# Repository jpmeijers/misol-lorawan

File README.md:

# LoRa Weather Station

__THIS IS STILL A WORK IN PROGRESS__

This repo contains a design for a replacement PCB for a MISOL weather station. The replacement PCB fits in the same space and enclosure as the original transmitter board. It sends the sensor data via a LoRa radio. The new PCB supports LoRaWAN and can send the data to a network like The Things Network.

The PCB design is done using KiCad.

# References

http://www.misolie.net/weather-station-c-43.html

https://www.robotics.org.za/WH-SP-WS02

https://www.sparkfun.com/products/8942

https://cdn.sparkfun.com/assets/8/4/c/d/6/Weather_Sensor_Assembly_Updated.pdf

# Original PCB

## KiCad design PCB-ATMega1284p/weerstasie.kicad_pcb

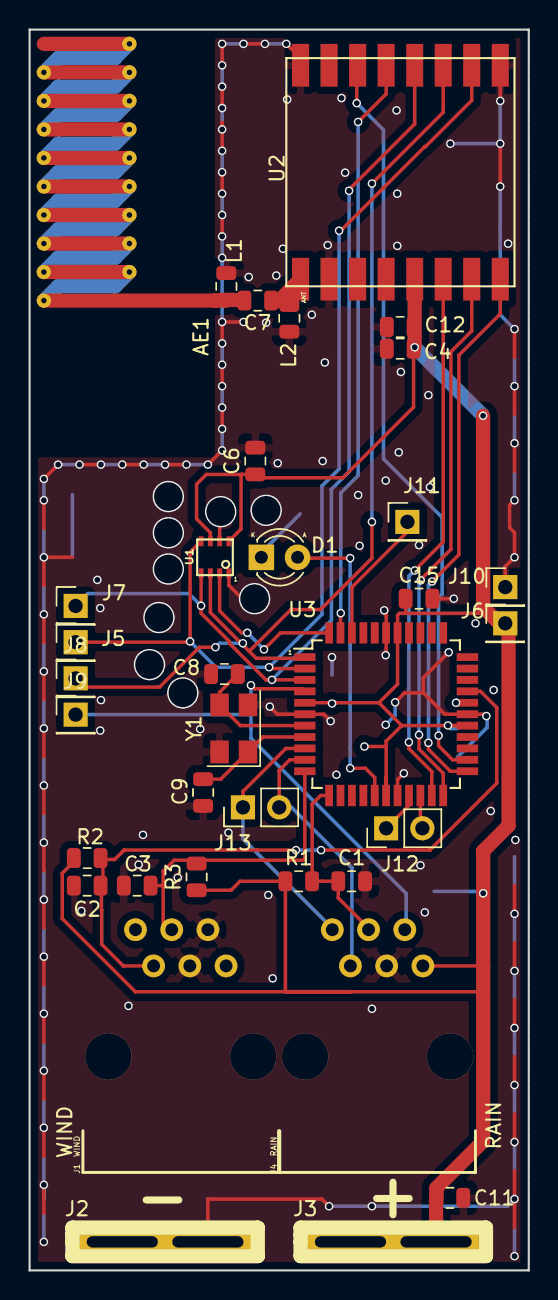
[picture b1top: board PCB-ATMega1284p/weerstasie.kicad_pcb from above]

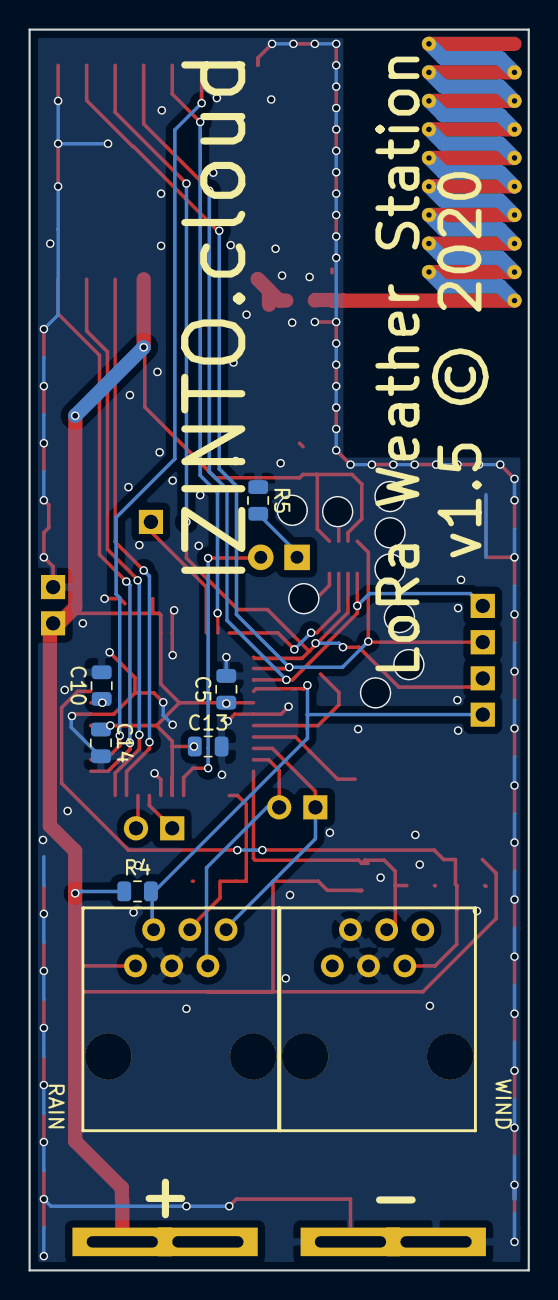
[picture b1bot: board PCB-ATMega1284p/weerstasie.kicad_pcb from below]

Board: 2 copper layers, 35.0 x 87.0 mm, 41 parts (6 on the bottom side), 27 nets.

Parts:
AE1: Antenna; PCB_HELICAL_ANTENNA_868
C1, C2, C3, C5, C6, C10, C12, C13, C14, C15: 100n; C_0805_2012Metric
C4, C11: 10u; C_0805_2012Metric
C7: 1pF; C_0805_2012Metric
C8, C9: 22p; C_0805_2012Metric
D1: LED; LED_D3.0mm
J1: WIND; TE_Connectivity_5520425-3
J2: batt -; BATTERY_TERMINAL
J3: batt +; BATTERY_TERMINAL
J4: RAIN; TE_Connectivity_5520425-3
J5, J6, J7, J8, J9, J10: Conn_01x01; Pin_Header_Straight_1x01_Pitch2.54mm
J11: INT2; Pin_Header_Straight_1x01_Pitch2.54mm
J12: I2C; Pin_Header_Straight_1x02_Pitch2.54mm
J13: UART; Pin_Header_Straight_1x02_Pitch2.54mm
L1: 12nH; L_0805_2012Metric
L2: NA; L_0805_2012Metric
R1, R2, R3, R4, R5: 10k; R_0805_2012Metric
U1: BME280
U2: RFM95
U3: ATMEGA1284P-AU; TQFP-44_10x10mm_Pitch0.8mm
Y1: Crystal_GND24; Crystal_SMD_5032-4Pin_5.0x3.2mm

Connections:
/BME_SS: U1.2, U3.44
/MISO: J5.1, U1.5, U2.2, U3.2
/MOSI: J8.1, U1.3, U2.3, U3.1
/RAIN: C1.1, J4.3, R1.2, U3.12
/RESET: J4.5, J9.1, R4.2, U3.4
/RFM_D0: U2.14, U3.21
/RFM_D1: U2.15, U3.22
/RFM_D2: U2.16, U3.23
/RFM_RESET: U2.6, U3.24
/RFM_SS: U2.5, U3.43
/SCK: J7.1, U1.4, U2.4, U3.3
/UART_RX: J4.1, J13.1, U3.9
/UART_TX: J4.2, J13.2, U3.10
/WIND_DIR: C2.1, J1.2, R2.2, U3.30
/WIND_SPEED: C3.1, J1.3, R3.2, U3.11
GND: C1.2, C2.2, C3.2, C4.2, C5.2, C6.2, C8.2, C9.2, C10.2, C11.2, C12.2, C13.2, C14.2, C15.2, J1.4, J1.5, J1.7, J1.8, J2.1, J4.4, J4.7, J4.8, J10.1, L1.1, L2.1, R5.1, U1.1, U1.7, U2.1, U2.8, U2.10, U3.6, U3.18, U3.28, U3.39, Y1.2, Y1.4
unnamed: AE1.1, C7.2, L1.2
unnamed: C7.1, L2.2, U2.9
unnamed: C8.1, U3.7, Y1.3
unnamed: C9.1, U3.8, Y1.1
unnamed: C10.1, U3.29
unnamed: D1.1, R5.2
unnamed: D1.2, U3.16
unnamed: J11.1, U3.42
unnamed: J12.1, U3.19
unnamed: J12.2, U3.20
VCC: C4.1, C5.1, C6.1, C11.1, C12.1, C13.1, C14.1, C15.1, J3.1, J4.6, J6.1, R1.1, R2.1, R3.1, R4.1, U1.6, U1.8, U2.13, U3.5, U3.17, U3.27, U3.38

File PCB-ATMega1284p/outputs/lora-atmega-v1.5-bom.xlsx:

| Designator | Quantity | Package | Description | Comment | LCSC Part Number(optional) | Manufacture Part Number | Manufacturer(optional) | URL
 | U2 | 1 | NiceRF LoRa | RFM95 |  |  | LORA1276-C1-868 | NiceRF | https://www.nicerf.com/product_146_198.html
 | U3 | 1 | TQFP-44_10x10mm_Pitch0.8mm | ATMEGA1284P-AU |  | C33575
 | D1 | 1 | LED_D3.0mm | LED |  | C99771
 | U1 | 1 | BME280 | BME280 |  | C92489
 | Y1 | 1 | Crystal_SMD_0603-4Pin_6.0x3.5mm | Crystal_GND24 |  | C133333
 | J1,J4 | 2 | SPARKFUN_RJ11-6 | WIND,RAIN |  | C305971
 | C1,C2,C3,C5,C6,C10,C12,C13,C14,C15 | 10 | C_0805_2012Metric | 100n | any cheapest option is ok
 | C4,C11 | 2 | C_0805_2012Metric | 10u | any cheapest option is ok
 | C7 | 1 | C_0805_2012Metric | 1pF | any cheapest option is ok
 | C8,C9 | 2 | C_0805_2012Metric | 22p | any cheapest option is ok
 | L1 | 1 | L_0805_2012Metric | 12nH |  | C75651
 | R1,R2,R3,R4,R5 | 5 | R_0805_2012Metric | 10k | any cheapest option is ok
 | L2 |  |  |  | DO NOT SOLDER
 | J6,J7,J8,J9,J10,J5 |  |  |  | DO NOT SOLDER
 | J2 |  |  |  | DO NOT SOLDER
 | J3 |  |  |  | DO NOT SOLDER
 | AE1 |  |  |  | DO NOT SOLDER
 | J11 |  |  |  | DO NOT SOLDER
 | J12 |  |  |  | DO NOT SOLDER
 | J13 |  |  |  | DO NOT SOLDER

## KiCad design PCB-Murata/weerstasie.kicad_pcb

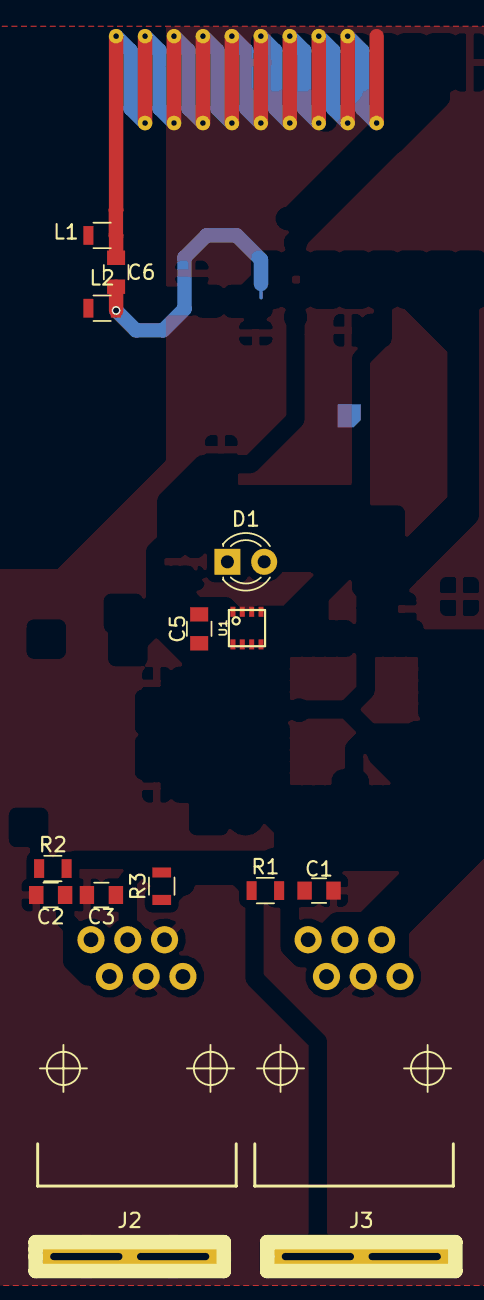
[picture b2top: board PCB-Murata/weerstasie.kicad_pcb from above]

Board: 2 copper layers, 18 parts (1 on the bottom side), 15 nets.

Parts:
AE1: Antenna; PCB_HELICAL_ANTENNA_868
C1, C2, C3, C5: 100n; C_0805
C6: 1pF; C_0805
D1: LED; LED_D3.0mm
J1: WIND; SPARKFUN_RJ11-6
J2: batt -; BATTERY_TERMINAL
J3: batt +; BATTERY_TERMINAL
J4: RAIN; SPARKFUN_RJ11-6
L1: 12nH; L_0805
L2: NA; L_0805
R1: 10k1; R_0805
R2: 10k2; R_0805
R3: 10k3; R_0805
U1: BME280
U2: CMWX1ZZABZ-078; XCVR_CMWX1ZZABZ-078

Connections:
/ANT_MCU: C6.1, L2.2, U2.26
/BME_SS: U1.2, U2.17
/MISO: U1.5, U2.15
/MOSI: U1.3, U2.14
/RAIN: C1.1, J4.3, R1.2, U2.42
/SCK: U1.4, U2.16
/SOLAR_1: J4.1, U2.33
/SOLAR_2: J4.2, U2.24
/SOLAR_5: J4.5, U2.23
/SOLAR_6: J4.6, U2.22
/WIND_DIR: C2.1, J1.2, R2.2
/WIND_SPEED: C3.1, J1.3, R3.2, U2.41
GND: C1.2, C2.2, C3.2, C5.2, J1.4, J1.5, J2.1, J4.4, L1.1, L2.1, U1.1, U1.7, U2.3, U2.7, U2.25, U2.27, U2.44, U2.49, U2.50, U2.51, U2.52, U2.53, U2.54, U2.55, U2.56, U2.57
unnamed: AE1.1, C6.2, L1.2
VCC: C5.1, J3.1, R1.1, R2.1, R3.1, U1.6, U1.8

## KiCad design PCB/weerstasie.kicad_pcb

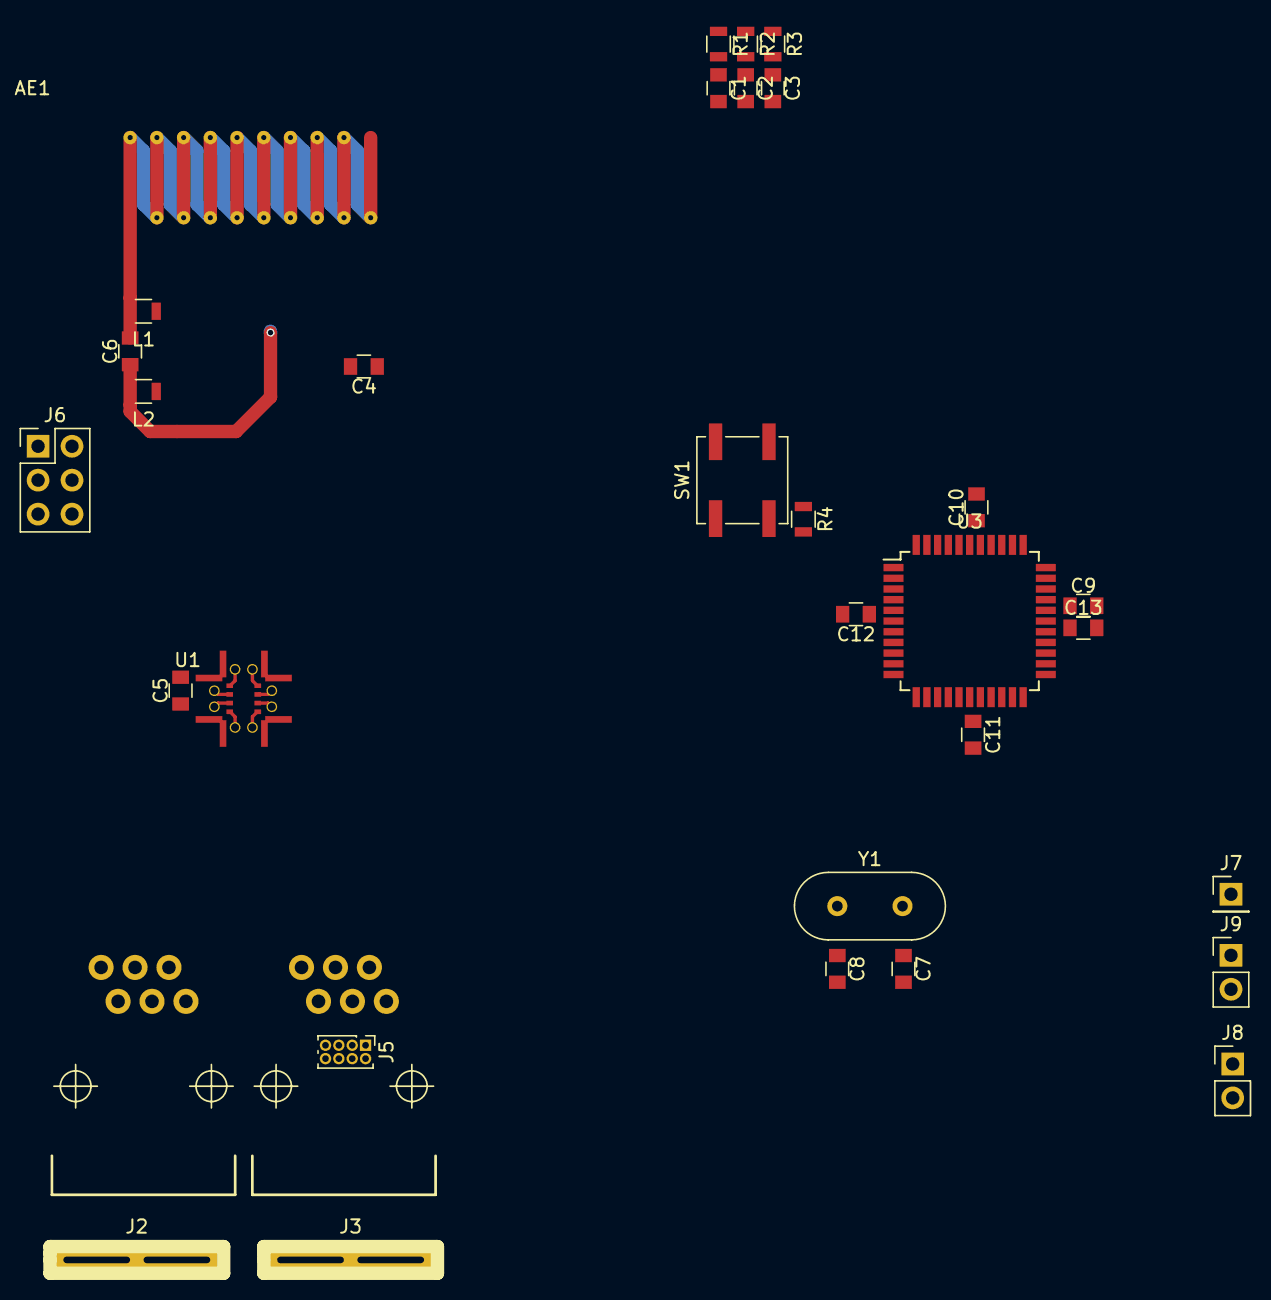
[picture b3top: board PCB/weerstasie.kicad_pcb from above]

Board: 2 copper layers, 34 parts (1 on the bottom side), 33 nets.

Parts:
AE1: Antenna; PCB_HELICAL_ANTENNA_868
C1, C2, C3, C4, C5: 100n; C_0805
C6: 1pF; C_0805
C7, C8: 22p; C_0805
C9, C10, C11, C12, C13: 100nF; C_0805
J1: WIND; SPARKFUN_RJ11-6
J2: batt -; BATTERY_TERMINAL
J3: batt +; BATTERY_TERMINAL
J4: RAIN; SPARKFUN_RJ11-6
J5: SolarSensJumpers; Pin_Header_Straight_2x04_Pitch1.00mm
J6: ICSP; Pin_Header_Straight_2x03_Pitch2.54mm
J7: INT2; Pin_Header_Straight_1x01_Pitch2.54mm
J8: I2C; Pin_Header_Straight_1x02_Pitch2.54mm
J9: UART; Pin_Header_Straight_1x02_Pitch2.54mm
L1: 12nH; L_0805
L2: NA; L_0805
R1: 10k1; R_0805
R2: 10k2; R_0805
R3: 10k3; R_0805
R4: 10k; R_0805
SW1: SW_Push; SW_SPST_B3SL-1002P
U1: BME280; BME280-handsoldering
U2: RFM95
U3: ATMEGA1284P-AU; TQFP-44_10x10mm_Pitch0.8mm
Y1: 8MHz; Crystal_HC49-U_Vertical

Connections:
/BME_SS: U1.2, U3.43
/MISO: J6.1, U1.5, U2.2, U3.2
/MOSI: J6.4, U1.3, U2.3, U3.1
/RAIN: C1.1, J4.3, R1.2, U3.12
/RESET: J6.5, R4.2, SW1.2, U3.4
/RFM_D0: U2.14, U3.21
/RFM_D1: U2.15, U3.22
/RFM_D2: U2.16, U3.23
/RFM_RESET: U2.6, U3.24
/RFM_SS: U2.5, U3.44
/SCK: J6.3, U1.4, U2.4, U3.3
/SOLAR_1: J5.8, U3.33
/SOLAR_2: J5.6, U3.32
/SOLAR_5: J5.4, U3.31
/SOLAR_6: J5.2, U3.30
/WIND_DIR: C2.1, J1.2, R2.2, U3.37
/WIND_SPEED: C3.1, J1.3, R3.2, U3.11
GND: C1.2, C2.2, C3.2, C4.2, C5.2, C7.2, C8.2, C9.2, C10.2, C11.2, C12.2, C13.2, J1.4, J1.5, J2.1, J4.4, J6.6, L1.1, L2.1, SW1.1, U1.1, U1.7, U2.1, U2.8, U2.10, U3.6, U3.18, U3.28, U3.39
unnamed: AE1.1, C6.2, L1.2
unnamed: C6.1, L2.2, U2.9
unnamed: C7.1, U3.7, Y1.2
unnamed: C8.1, U3.8, Y1.1
unnamed: C9.1, U3.29
unnamed: J4.1, J5.7
unnamed: J4.2, J5.5
unnamed: J4.5, J5.3
unnamed: J4.6, J5.1
unnamed: J7.1, U3.42
unnamed: J8.1, U3.19
unnamed: J8.2, U3.20
unnamed: J9.1, U3.9
unnamed: J9.2, U3.10
VCC: C4.1, C5.1, C10.1, C11.1, C12.1, C13.1, J3.1, J6.2, R1.1, R2.1, R3.1, R4.1, U1.6, U1.8, U2.13, U3.5, U3.17, U3.27, U3.38

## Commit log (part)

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2018-08-26 Add images of the original pcb
2018-08-26 Fixed images in readme
2018-08-26 Add missing connections in schematic
2018-08-27 Ready to be routed
2018-08-31 Finish PCB layout and rename
2018-08-31 Copy design and replace ATmega and RFM95 with Murata LoRa module
2018-09-01 Some PCB cleanup
2018-09-01 Some starting connections for murata
2018-09-01 More cleanup and comaptibility with allpcb
2018-09-01 Include Gerbers as ordered from AllPCB
2018-09-01 Add ventilation holes/vias around thermometer and resend gerbers to AllPCB
2019-02-20 Update to kicad 5 Move rj11's closer together
2019-05-27 Fix RJ11 solder mask. Add v1.4 label. Order from JLC.
2020-07-18 Remove solar connections. Add uart on rain rj12.
2020-07-20 Misol Lora Atmega V1.5 order placed with PCBgogo

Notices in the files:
PCB-ATMega1284p/weerstasie.kicad_pcb:
v1.5 © 2020
